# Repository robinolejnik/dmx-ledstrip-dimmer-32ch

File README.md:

# 32ch DMX LED Strip Dimmer

Arduino Mini and TLC5940 based 32 channel 12V PWM dimmer with [DMX512](https://en.wikipedia.org/wiki/DMX512) and [RDM](https://en.wikipedia.org/wiki/RDM_(lighting)) support.

## Table of contents
* [Features](#features)
* [Building and connecting the PCB](#building-and-connecting-the-pcb)
* [Installing the Software](#installing-the-software)
* [Setting the DMX channel](#setting-the-dmx-channel)
* [Write your own Software](#write-your-own-software)
* [Arduino Pin Configuration](#arduino-pin-configuration)
* [Contributing](#contributing)
* [See also](#see-also)
* [License](#license)

## Features
- 32 channels
- several amps current capability per channel
- high PWM frequency
- [DMX512](https://en.wikipedia.org/wiki/DMX512) with [RDM](https://en.wikipedia.org/wiki/RDM_(lighting)) support
- control LEDs, LED-Strips, Lamps, Motors, Relays, ...

## Building and connecting the PCB
The double sided PCB has surface mounted components on both sides. All resistors and capacitors are 0805 sized parts.
Screw terminals are available for all connections.

### Installing the Software

#### Connecting the Programmer
On the PCB, there is no dedicated programming connector. Instead, directly connect a serial adapter to the Arduino Pro Mini. Make sure that no DMX device is connected to the PCB.

#### Libraries
Install the required libraries within the Arduino IDE
* [tlc5940](https://github.com/PaulStoffregen/Tlc5940) Control of the two TLC5940 ICs
* [dmxserial2](https://github.com/mathertel/DmxSerial2) Used to handle DMX and RDM decoding

Open the [Sketch](dmx_led_strip_dimmer_32ch.ino) with the Arduino IDE, change the DMX address if needed, select the correct serial port and Hardware (Arduino Pro Mini or Arduino Mini) and click Upload.

### Setting the DMX channel
The DMX channel can be preset in the Arduino source code. Later, it can only be changed via RDM ([Remote Device Management](https://en.wikipedia.org/wiki/RDM_(lighting))) commands.

## Write your own Software
The PWM signals are created by two chained TLC5940 PWM LED drivers. Output 1-16 of U7 maps to Output 1-16 on the PCB, output 1-16 of U8 maps to Output 17-32 of the PCB. Per channel, one 74HC04 inverter is used. It is necessary because the PWM controller cannot completely turn off a directly connected N-channel MOSFET. It cannot get it's PWM count down to 0. By inverting the PWM signal, the PCB output can be turned off by fully turning on the TLC5940 channel.

### Arduino pin configuration

| Pin | Function              |
| --- | --------------------- |
|  0  | RxD (DMX)             |
|  1  | TxD (DMX)             |
|  2  | RS485 (DMX) Direction |
|  3  | GSCLK (TLC5940)       |
|  9  | XLAT (TLC5940)        |
| 10  | BLANK (TLC5940)       |
| 11  | SIN (TLC5940)         |
| 13  | SCLK (TLC5940)        |

Unlisted pins are not connected. The internal voltage regulator on the Arduino Mini Board is not used.

Take a look at the [schematic](schematic.pdf) too. It should clarify things further.

## Contributing
If you want to improve something, feel free to create a pull request.

One thing to optimize is the linear voltage regulator. Maybe someone is interested in fitting a suitable step down converter into the PCB?

## See also

* [TLC5940 datasheet](https://www.ti.com/lit/ds/symlink/tlc5940.pdf)
* [Wikipedia DMX512](https://en.wikipedia.org/wiki/DMX512)
* [Wikipedia RDM](https://en.wikipedia.org/wiki/RDM_(lighting))

## License
[MIT](https://choosealicense.com/licenses/mit/)

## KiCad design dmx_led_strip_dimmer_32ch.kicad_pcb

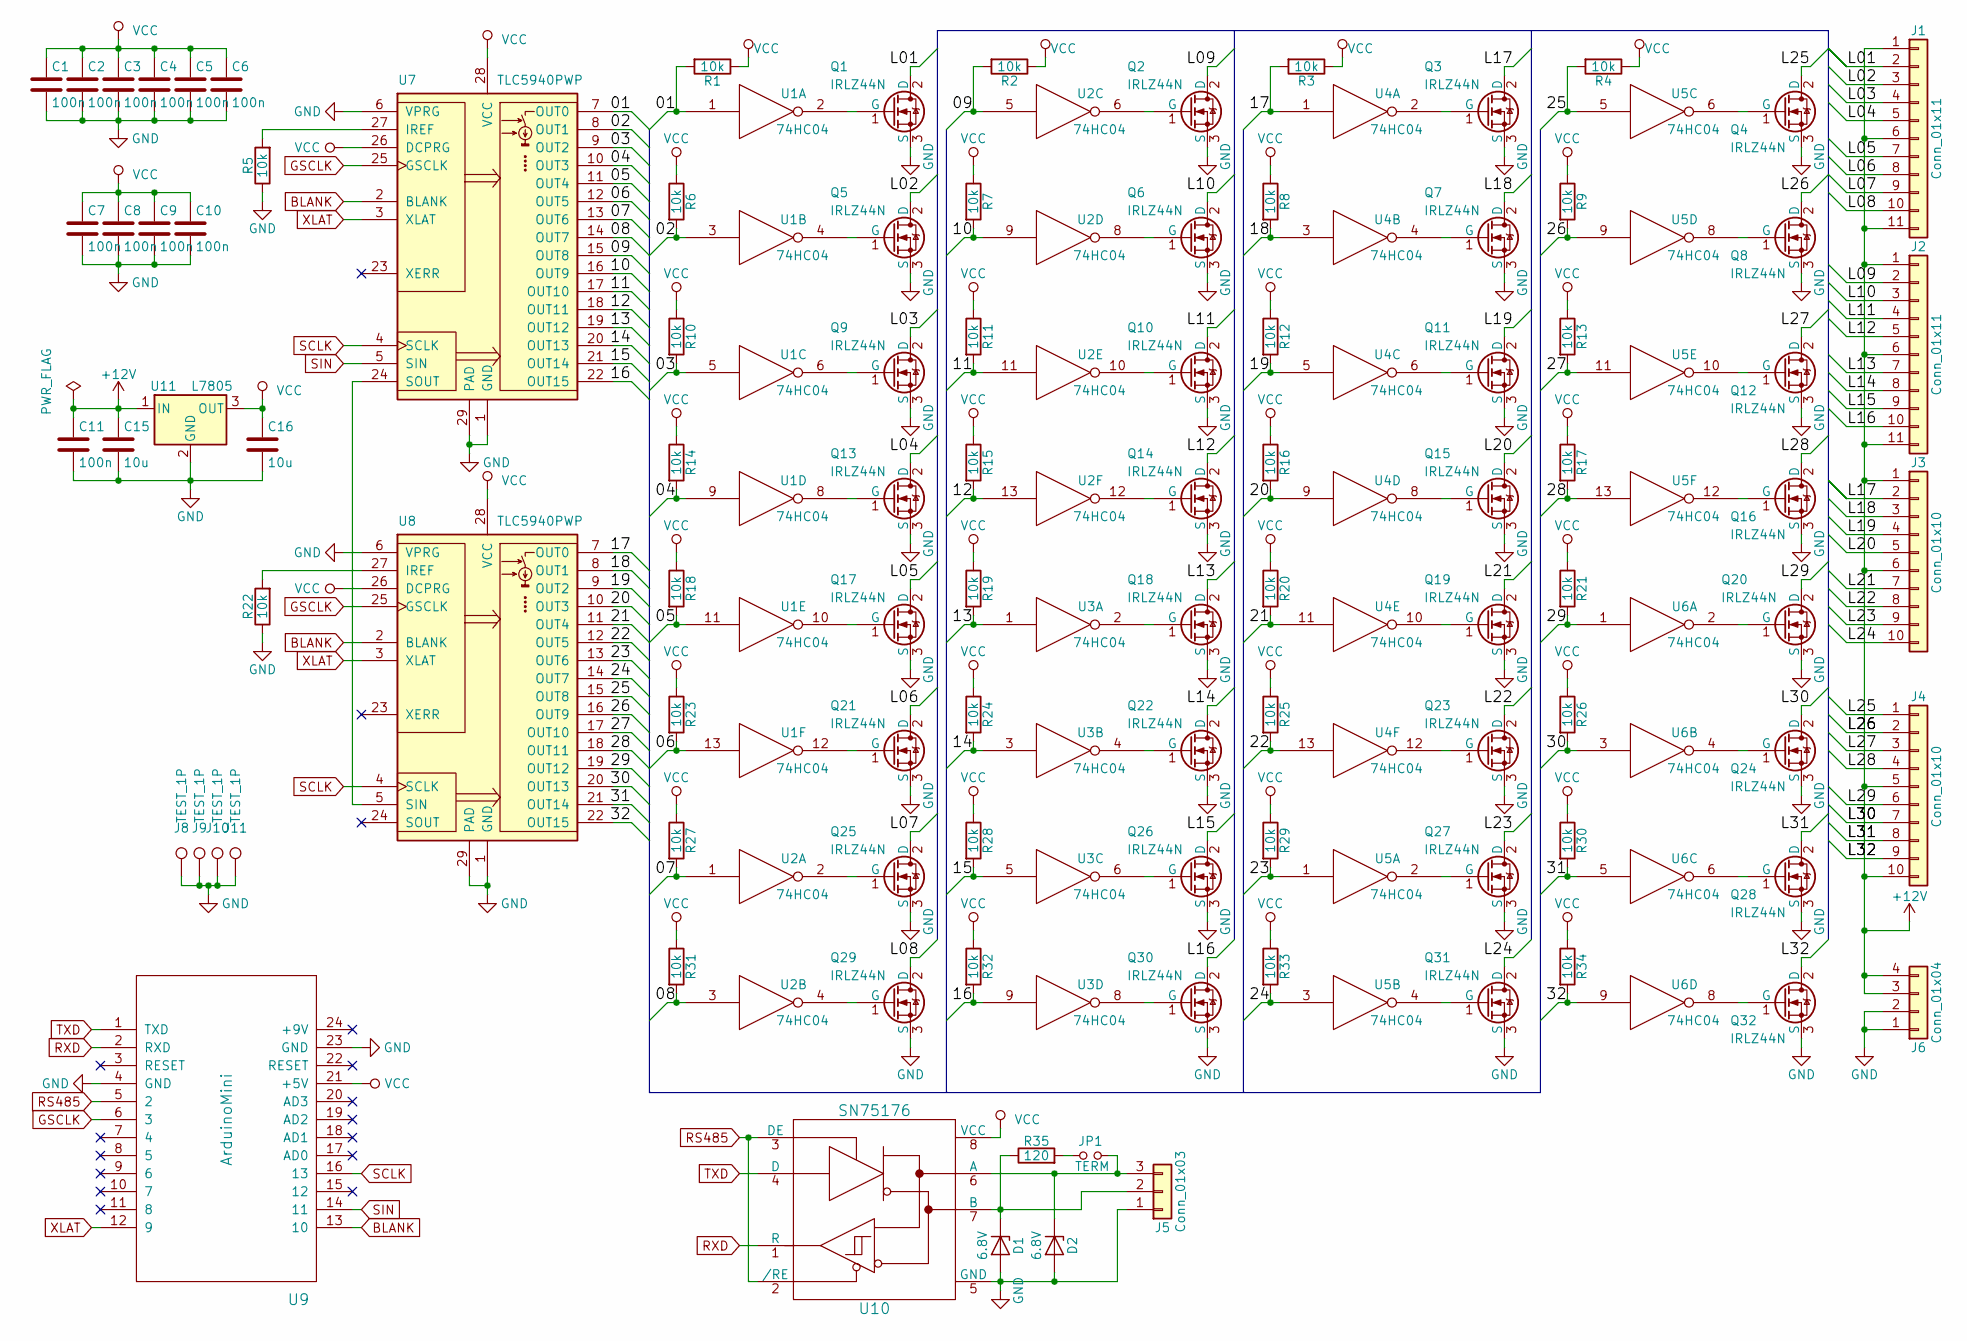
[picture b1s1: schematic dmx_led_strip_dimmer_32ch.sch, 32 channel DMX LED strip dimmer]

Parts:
C1, C2, C3, C4, C5, C6, C7, C8, C9, C10, C11: 100n; C_0805_HandSoldering
C15, C16: 10u; C_0805_HandSoldering
D1, D2: 6.8V; D_MiniMELF
J1, J2: Conn_01x11; TerminalBlock_Pheonix_MKDS1.5-11pol
J3, J4: Conn_01x10; TerminalBlock_Pheonix_MKDS1.5-10pol
J5: Conn_01x03; TerminalBlock_Pheonix_MKDS1.5-3pol
J6: Conn_01x04; TerminalBlock_Pheonix_MKDS1.5-4pol
J8, J9, J10, J11: TEST_1P; MountingHole_3.2mm_M3_ISO7380_Pad
JP1: TERM; Pin_Header_Straight_1x02_Pitch2.54mm
Q1, Q2, Q3, Q4, Q5, Q6, Q7, Q8, Q9, Q10, Q11, Q12, Q13, Q14, Q15, Q16, Q17, Q18, Q19, Q20, Q21, Q22, Q23, Q24, Q25, Q26, Q27, Q28, Q29, Q30, Q31, Q32: IRLZ44N; TO-220_Vertical
R1, R2, R3, R4, R5, R6, R7, R8, R9, R10, R11, R12, R13, R14, R15, R16, R17, R18, R19, R20, R21, R22, R23, R24, R25, R26, R27, R28, R29, R30, R31, R32, R33, R34: 10k; R_0805_HandSoldering
R35: 120; R_0805_HandSoldering
U1, U2, U3, U4, U5, U6: 74HC04; SOIC-14_3.9x8.7mm_Pitch1.27mm
U7, U8: TLC5940PWP; TSSOP-28_4.4x9.7mm_Pitch0.65mm
U9: ArduinoMini; DIP-24_W15.24mm_LongPads
U10: SN75176; SOIC-8_3.9x4.9mm_Pitch1.27mm
U11: L7805; TO-220-3_Vertical

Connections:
+12V: C11.1, C15.1, J1.1, J1.6, J1.11, J2.1, J2.6, J2.11, J3.1, J3.6, J4.5, J4.10, J6.3, J6.4, U11.1 (IN)
/01: R1.2, U1.1, U7.7 (OUT0)
/02: R6.2, U1.3, U7.8 (OUT1)
/03: R10.2, U1.5, U7.9 (OUT2)
/04: R14.2, U1.9, U7.10 (OUT3)
/05: R18.2, U1.11, U7.11 (OUT4)
/06: R23.2, U1.13, U7.12 (OUT5)
/07: R27.2, U2.1, U7.13 (OUT6)
/08: R31.2, U2.3, U7.14 (OUT7)
/09: R2.2, U2.5, U7.15 (OUT8)
/10: R7.2, U2.9, U7.16 (OUT9)
/11: R11.2, U2.11, U7.17 (OUT10)
/12: R15.2, U2.13, U7.18 (OUT11)
/13: R19.2, U3.1, U7.19 (OUT12)
/14: R24.2, U3.3, U7.20 (OUT13)
/15: R28.2, U3.5, U7.21 (OUT14)
/16: R32.2, U3.9, U7.22 (OUT15)
/17: R3.2, U4.1, U8.7 (OUT0)
/18: R8.2, U4.3, U8.8 (OUT1)
/19: R12.2, U4.5, U8.9 (OUT2)
/20: R16.2, U4.9, U8.10 (OUT3)
/21: R20.2, U4.11, U8.11 (OUT4)
/22: R25.2, U4.13, U8.12 (OUT5)
/23: R29.2, U5.1, U8.13 (OUT6)
/24: R33.2, U5.3, U8.14 (OUT7)
/25: R4.2, U5.5, U8.15 (OUT8)
/26: R9.2, U5.9, U8.16 (OUT9)
/27: R13.2, U5.11, U8.17 (OUT10)
/28: R17.2, U5.13, U8.18 (OUT11)
/29: R21.2, U6.1, U8.19 (OUT12)
/30: R26.2, U6.3, U8.20 (OUT13)
/31: R30.2, U6.5, U8.21 (OUT14)
/32: R34.2, U6.9, U8.22 (OUT15)
/L01: J1.2, Q1.2 (D)
/L02: J1.3, Q5.2 (D)
/L03: J1.4, Q9.2 (D)
/L04: J1.5, Q13.2 (D)
/L05: J1.7, Q17.2 (D)
/L06: J1.8, Q21.2 (D)
/L07: J1.9, Q25.2 (D)
/L08: J1.10, Q29.2 (D)
/L09: J2.2, Q2.2 (D)
/L10: J2.3, Q6.2 (D)
/L11: J2.4, Q10.2 (D)
/L12: J2.5, Q14.2 (D)
/L13: J2.7, Q18.2 (D)
/L14: J2.8, Q22.2 (D)
/L15: J2.9, Q26.2 (D)
/L16: J2.10, Q30.2 (D)
/L17: J3.2, Q3.2 (D)
/L18: J3.3, Q7.2 (D)
/L19: J3.4, Q11.2 (D)
/L20: J3.5, Q15.2 (D)
/L21: J3.7, Q19.2 (D)
/L22: J3.8, Q23.2 (D)
/L23: J3.9, Q27.2 (D)
/L24: J3.10, Q31.2 (D)
/L25: J4.1, Q4.2 (D)
/L26: J4.2, Q8.2 (D)
/L27: J4.3, Q12.2 (D)
/L28: J4.4, Q16.2 (D)
/L29: J4.6, Q20.2 (D)
/L30: J4.7, Q24.2 (D)
/L31: J4.8, Q28.2 (D)
/L32: J4.9, Q32.2 (D)
BLANK: U7.2 (BLANK), U8.2 (BLANK), U9.13 (10)
GND: C1.2, C2.2, C3.2, C4.2, C5.2, C6.2, C7.2, C8.2, C9.2, C10.2, C11.2, C15.2, C16.2, D1.2 (A), D2.2 (A), J5.1, J6.1, J6.2, J8.1, J9.1, J10.1, J11.1, Q1.3 (S), Q2.3 (S), Q3.3 (S), Q4.3 (S), Q5.3 (S), Q6.3 (S), Q7.3 (S), Q8.3 (S), Q9.3 (S), Q10.3 (S), Q11.3 (S), Q12.3 (S), Q13.3 (S), Q14.3 (S), Q15.3 (S), Q16.3 (S), Q17.3 (S), Q18.3 (S), Q19.3 (S), Q20.3 (S), Q21.3 (S), Q22.3 (S), Q23.3 (S), Q24.3 (S), Q25.3 (S), Q26.3 (S), Q27.3 (S), Q28.3 (S), Q29.3 (S), Q30.3 (S), Q31.3 (S), Q32.3 (S), R5.1, R22.1, U1.7 (GND), U2.7 (GND), U3.7 (GND), U4.7 (GND), U5.7 (GND), U6.7 (GND), U7.1 (GND), U7.6 (VPRG), U7.29 (PAD), U8.1 (GND), U8.6 (VPRG), U8.29 (PAD), U9.4 (GND), U9.23 (GND), U10.5 (GND), U11.2 (GND)
GSCLK: U7.25 (GSCLK), U8.25 (GSCLK), U9.6 (3)
unnamed: D1.1 (K), J5.2, R35.1, U10.7 (B)
unnamed: D2.1 (K), J5.3, JP1.2, U10.6 (A)
unnamed: JP1.1, R35.2
unnamed: Q1.1 (G), U1.2
unnamed: Q2.1 (G), U2.6
unnamed: Q3.1 (G), U4.2
unnamed: Q4.1 (G), U5.6
unnamed: Q5.1 (G), U1.4
unnamed: Q6.1 (G), U2.8
unnamed: Q7.1 (G), U4.4
unnamed: Q8.1 (G), U5.8
unnamed: Q9.1 (G), U1.6
unnamed: Q10.1 (G), U2.10
unnamed: Q11.1 (G), U4.6
unnamed: Q12.1 (G), U5.10
unnamed: Q13.1 (G), U1.8
unnamed: Q14.1 (G), U2.12
unnamed: Q15.1 (G), U4.8
unnamed: Q16.1 (G), U5.12
unnamed: Q17.1 (G), U1.10
unnamed: Q18.1 (G), U3.2
unnamed: Q19.1 (G), U4.10
unnamed: Q20.1 (G), U6.2
unnamed: Q21.1 (G), U1.12
unnamed: Q22.1 (G), U3.4
unnamed: Q23.1 (G), U4.12
unnamed: Q24.1 (G), U6.4
unnamed: Q25.1 (G), U2.2
unnamed: Q26.1 (G), U3.6
unnamed: Q27.1 (G), U5.2
unnamed: Q28.1 (G), U6.6
unnamed: Q29.1 (G), U2.4
unnamed: Q30.1 (G), U3.8
unnamed: Q31.1 (G), U5.4
unnamed: Q32.1 (G), U6.8
unnamed: R5.2, U7.27 (IREF)
unnamed: R22.2, U8.27 (IREF)
unnamed: U7.24 (SOUT), U8.5 (SIN)
RS485: U9.5 (2), U10.2 (/RE), U10.3 (DE)
RXD: U9.2 (RXD), U10.1 (R)
SCLK: U7.4 (SCLK), U8.4 (SCLK), U9.16 (13)
SIN: U7.5 (SIN), U9.14 (11)
TXD: U9.1 (TXD), U10.4 (D)
VCC: C1.1, C2.1, C3.1, C4.1, C5.1, C6.1, C7.1, C8.1, C9.1, C10.1, C16.1, R1.1, R2.1, R3.1, R4.1, R6.1, R7.1, R8.1, R9.1, R10.1, R11.1, R12.1, R13.1, R14.1, R15.1, R16.1, R17.1, R18.1, R19.1, R20.1, R21.1, R23.1, R24.1, R25.1, R26.1, R27.1, R28.1, R29.1, R30.1, R31.1, R32.1, R33.1, R34.1, U1.14 (VCC), U2.14 (VCC), U3.14 (VCC), U4.14 (VCC), U5.14 (VCC), U6.14 (VCC), U7.26 (DCPRG), U7.28 (VCC), U8.26 (DCPRG), U8.28 (VCC), U9.21 (+5V), U10.8 (VCC), U11.3 (OUT)
XLAT: U7.3 (XLAT), U8.3 (XLAT), U9.12 (9)

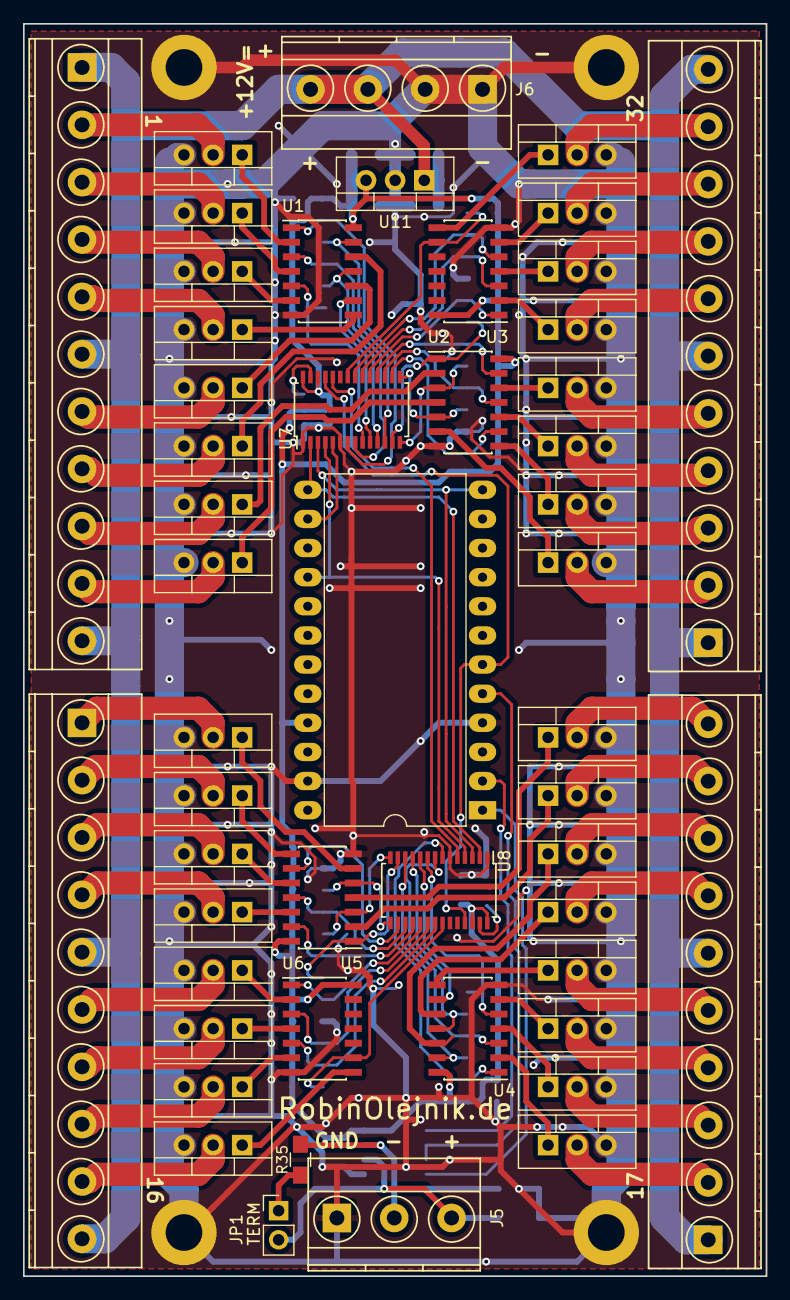
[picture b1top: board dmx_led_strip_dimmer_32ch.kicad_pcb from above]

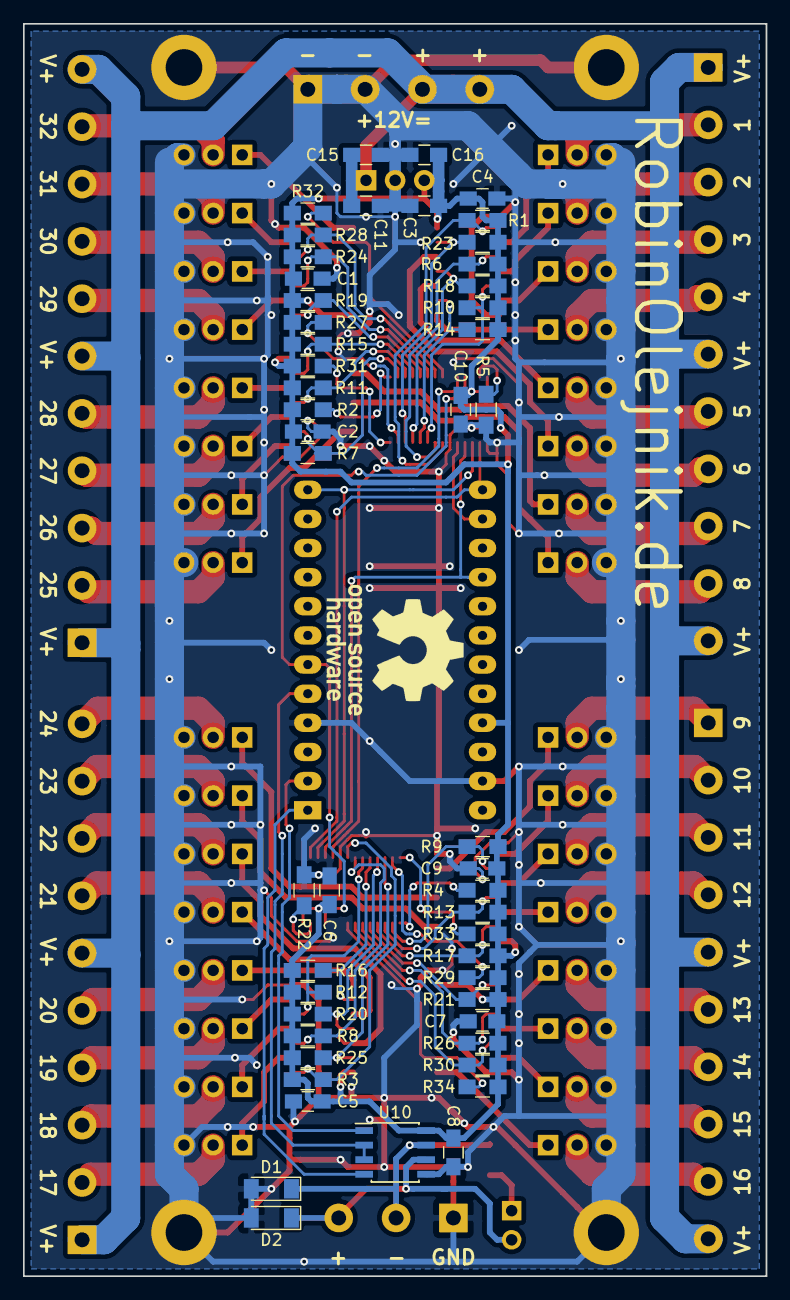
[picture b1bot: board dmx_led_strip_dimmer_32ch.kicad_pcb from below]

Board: 2 copper layers, 64.8 x 109.2 mm, 104 parts (50 on the bottom side), 113 nets.

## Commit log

2018-06-18 Added pcb files
2018-06-18 Added arduino sketch
2019-03-06 Updated schematic to KiCad 5
2019-03-06 Archived project for better portability
2019-11-24 added readme
2019-11-24 corrected some readme errors
2020-09-15 Readme update (Added and corrected links)
2020-09-15 Corrected a misspelling on the TLC5940 part name
2020-09-15 Removed the unnecessary cache dcm file.
2020-09-15 Added schematic.pdf
2024-05-09 Add MIT License
